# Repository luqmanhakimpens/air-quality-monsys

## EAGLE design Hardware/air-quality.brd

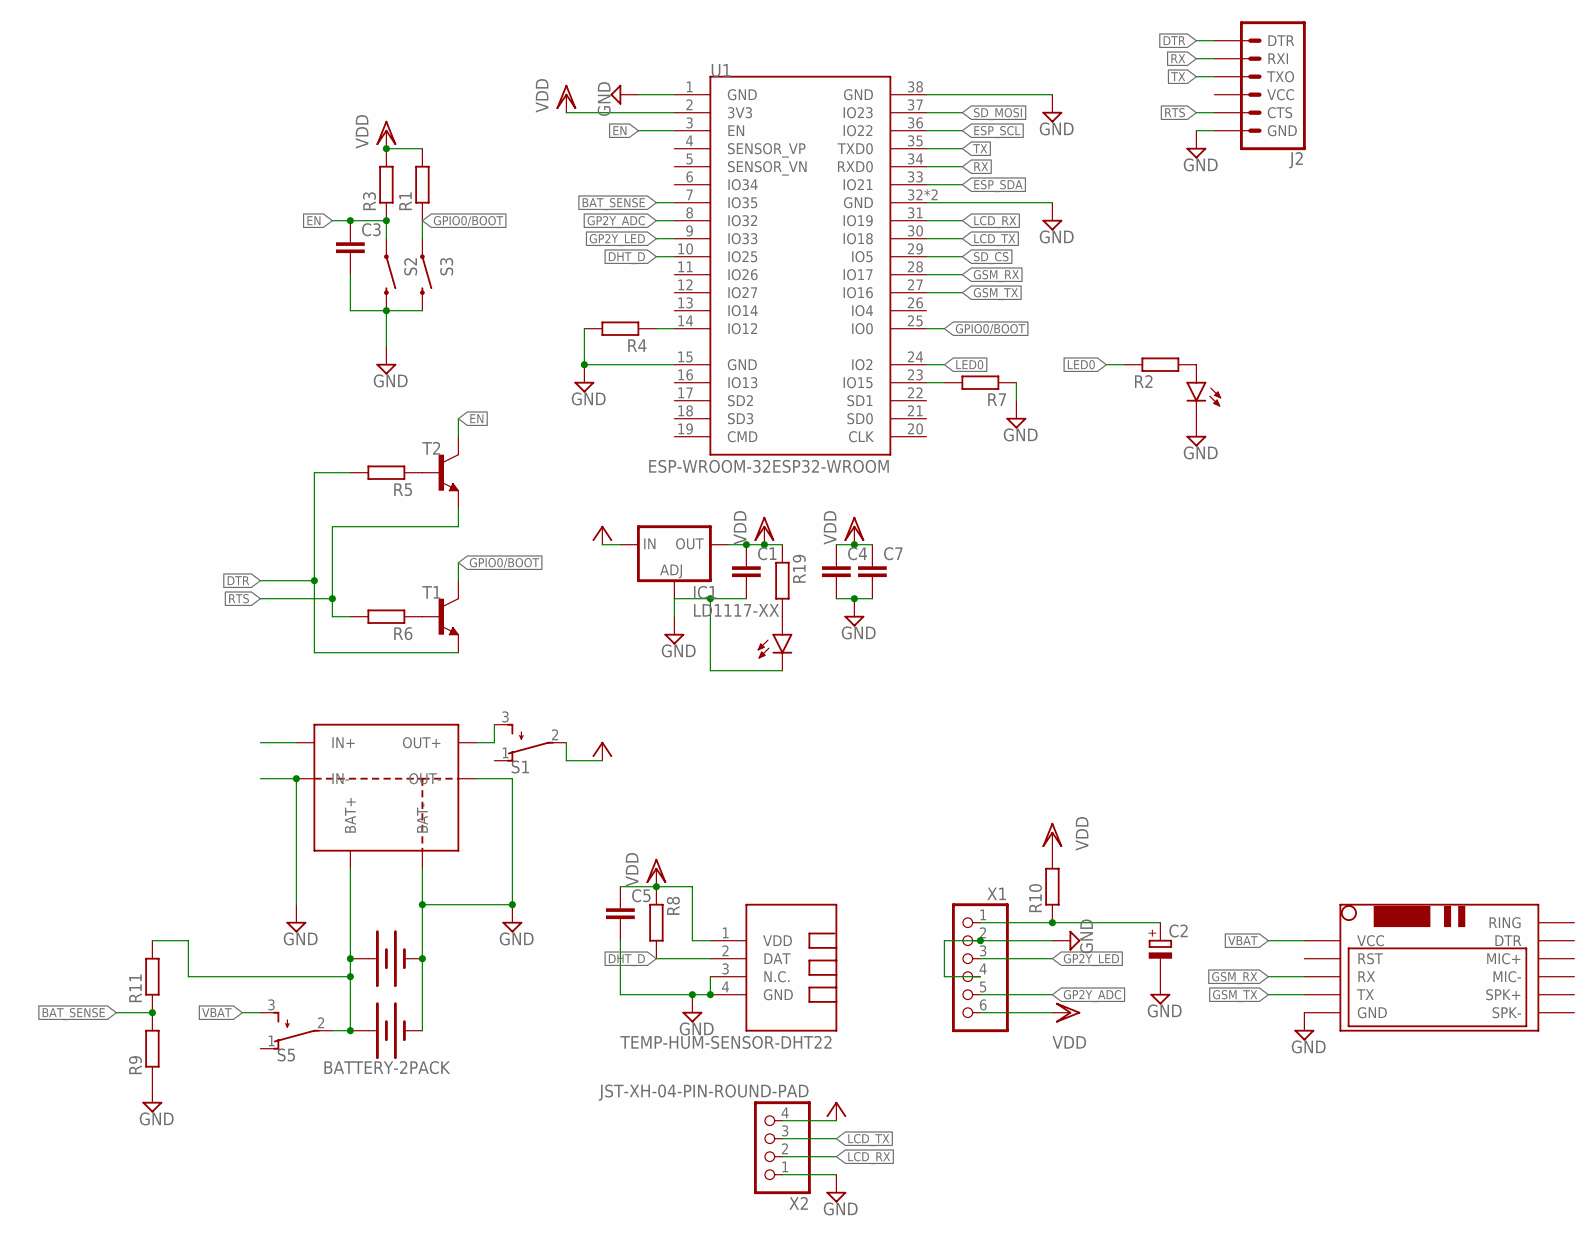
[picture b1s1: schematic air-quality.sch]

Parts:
C1, C3, C4, C5, C7: C-EUC0805; C0805
C2: CPOL-EUE2.5-6; E2,5-6
IC1: LD1117-XX; SOT230P700X180-4N
J2: 6_PIN_SERIAL_TARGETFEMALE; 6_PIN_SERIAL_TARGET_SIDE_W_SILK-FEMALE
LED12: LEDCHIP-LED0805; CHIP-LED0805
POW: LEDCHIP-LED0603; CHIP-LED0603
R1, R2, R3, R4, R5, R6, R7, R8, R9, R11, R19: R-EU_R0805; R0805
R10: R-EU_0204/7; 0204/7
S1, S5: TL32PO; TL3XPO
S2: ESP_BOOT; TACTILE-SWITCH-1101NE
S3: ESP_EN; TACTILE-SWITCH-1101NE
T1, T2: BC808-NPN-SOT23-BEC; SOT23-BEC
U1: ESP-WROOM-32ESP32-WROOM; ESP-WROOM-32
U$1: BMS-LITHIUM
U$2: BATTERY-2PACK; BATTERY-18650-HOLDER-2PACK-SMD
U$3: TEMP-HUM-SENSOR-DHT22
U$4: SIM800LMODULE
X1: JST-XH-06-PIN-ROUND-PAD; JST-XH-06-PACKAGE-ROUND-PAD
X2: JST-XH-04-PIN-ROUND-PAD; JST-XH-04-PACKAGE-ROUND-PAD

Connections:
BAT_SENSE: R9.2, R11.1, U1.7 (IO35)
DHT_D: R8.2, U1.10 (IO25), U$3.2 (DAT)
DTR: J2.1 (DTR), R5.2, T1.E
EN: C3.1, R3.1, S2.1, T2.C, U1.3 (EN)
ESP_SCL: U1.36 (IO22)
ESP_SDA: U1.33 (IO21)
GND: C1.2, C2.-, C3.2, C4.2, C5.2, C7.2, IC1.1 (ADJ), J2.6 (GND), LED12.C, POW.C, R4.2, R7.1, R9.1, S2.2, S3.2, U1.1 (GND), U1.15 (GND), U1.32 (GND), U1.38 (GND), U1.GND, U$1.BAT-, U$1.IN-, U$1.OUT-, U$2.-0, U$2.-1, U$3.3 (N.C.), U$3.4 (GND), U$4.GND, X1.2, X1.4, X2.1
GP2Y_ADC: U1.8 (IO32), X1.5
GP2Y_LED: U1.9 (IO33), X1.3
GPIO0/BOOT: R1.1, S3.1, T1.C, U1.25 (IO0)
GSM_RX: U1.28 (IO17), U$4.RX
GSM_TX: U1.27 (IO16), U$4.TX
LCD_RX: U1.31 (IO19), X2.2
LCD_TX: U1.30 (IO18), X2.3
LED0: R2.1, U1.24 (IO2)
unnamed: R5.1, T2.B
unnamed: R4.1, U1.14 (IO12)
unnamed: R7.2, U1.23 (IO15)
unnamed: LED12.A, R2.2
unnamed: R6.1, T1.B
unnamed: C2.+, R10.1, X1.1
unnamed: S1.3 (S), U$1.OUT+
unnamed: POW.A, R19.2
RTS: J2.5 (CTS), R6.2, T2.E
RX: J2.3 (RXI), U1.34 (RXD0)
SD_CS: U1.29 (IO5)
SD_MOSI: U1.37 (IO23)
TX: J2.2 (TXO), U1.35 (TXD0)
VB: R11.2, S5.2, U$1.BAT+, U$2.+0, U$2.+1
VBAT: S5.3 (S), U$4.VCC
VCC: IC1.3 (IN), S1.2, X2.4
VDD: C1.1, C4.1, C5.1, C7.1, IC1.2 (OUT), IC1.4 (OUT), R1.2, R3.2, R8.1, R10.2, R19.1, U1.2 (3V3), U$3.1 (VDD), X1.6

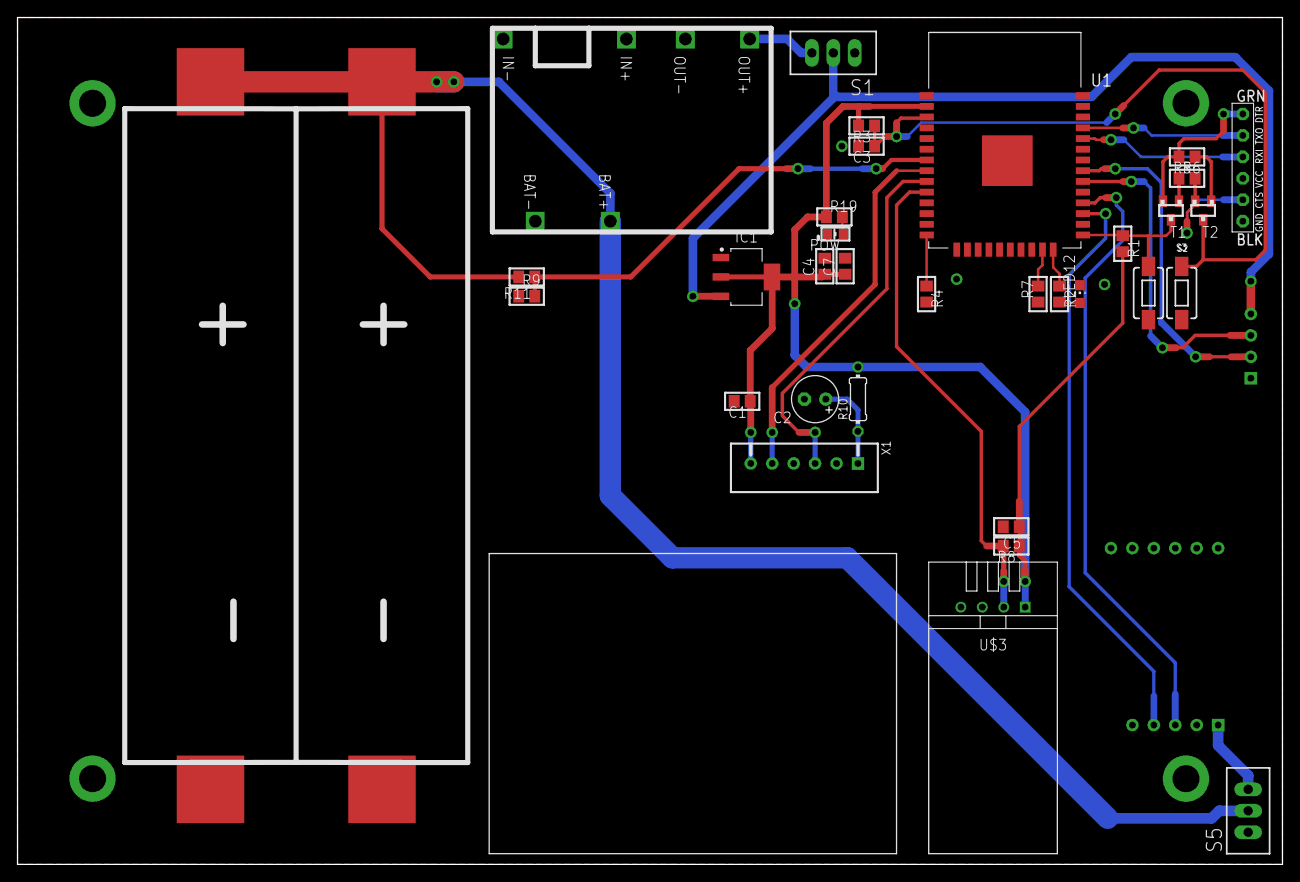
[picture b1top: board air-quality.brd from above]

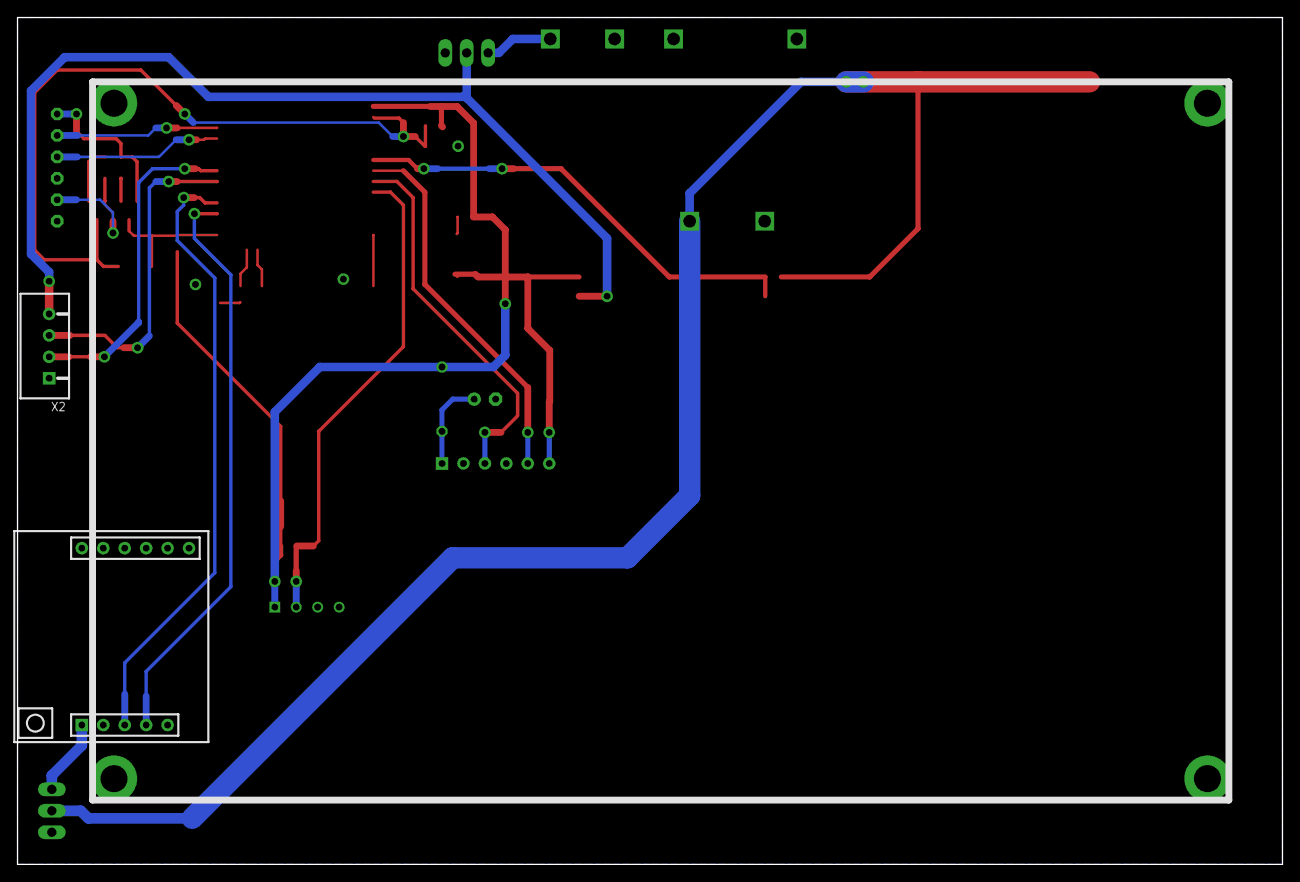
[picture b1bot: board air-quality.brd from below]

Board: 2 copper layers, 149.9 x 100.3 mm, 35 parts (2 on the bottom side), 28 nets.

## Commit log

2021-02-02 init
2021-02-02 add nextian editor files
2021-02-02 remove telegram token

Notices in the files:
parts and their libraries:
dht22: Released under the Creative Commons Attribution 4.0 International License: http://creativecommons.org/licenses/by/4.0
